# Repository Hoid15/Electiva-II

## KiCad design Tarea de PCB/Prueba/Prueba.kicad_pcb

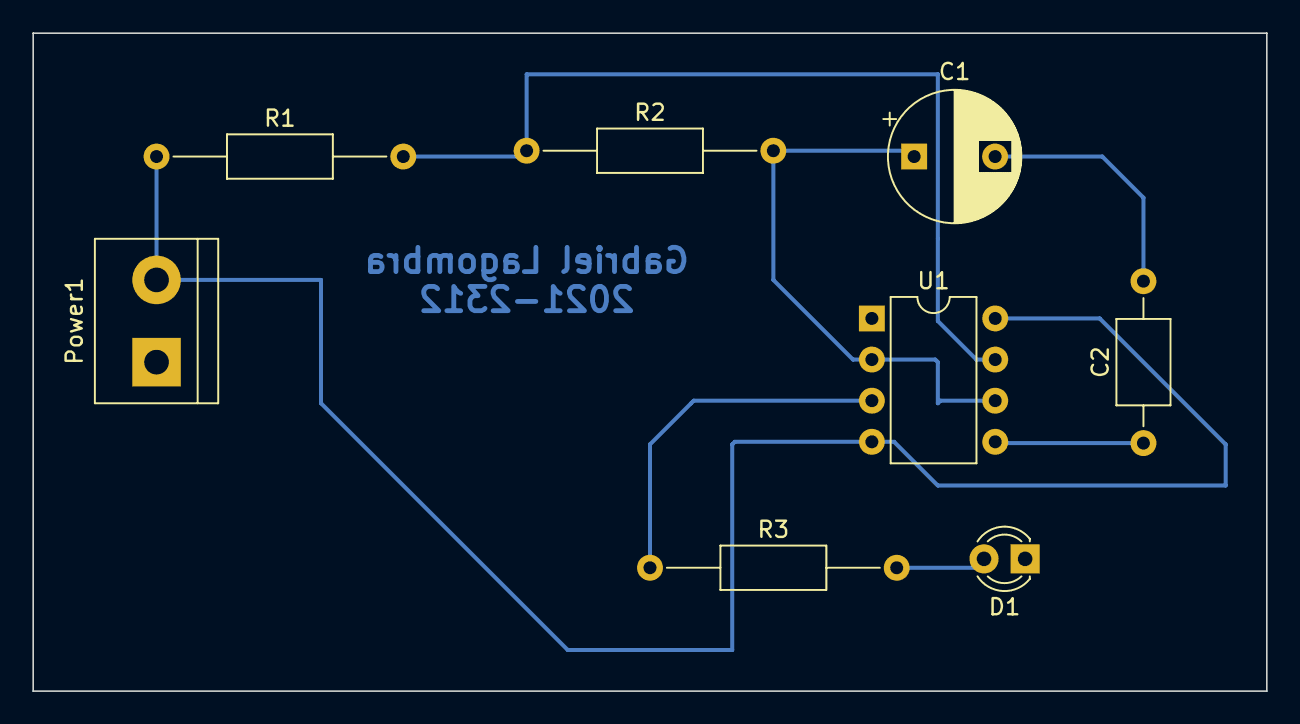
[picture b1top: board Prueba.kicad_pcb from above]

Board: 2 copper layers, 76.2 x 40.6 mm, 8 parts (0 on the bottom side), 7 nets.

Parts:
C1: 47uf; CP_Radial_D8.0mm_P5.00mm
C2: 100nf; C_Axial_L5.1mm_D3.1mm_P10.00mm_Horizontal
D1: LED; LED_D3.0mm
Power1: Screw_Terminal_01x02; TerminalBlock_bornier-2_P5.08mm
R1: 2.2K; R_Axial_DIN0207_L6.3mm_D2.5mm_P15.24mm_Horizontal
R2: 3.3K; R_Axial_DIN0207_L6.3mm_D2.5mm_P15.24mm_Horizontal
R3: 330; R_Axial_DIN0207_L6.3mm_D2.5mm_P15.24mm_Horizontal
U1: LM555xN; DIP-8_W7.62mm

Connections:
5+V: Power1.2, R1.1, U1.4 (R), U1.8 (VCC)
Led1: R3.1, U1.3 (Q)
unnamed: D1.2 (A), R3.2
unnamed: C2.1, U1.5 (CV)
SA2-6: C1.1, R2.2, U1.2 (TR), U1.6 (THR)
SA7: R1.2, R2.1, U1.7 (DIS)
gnd: C1.2, C2.2, D1.1 (K), Power1.1, U1.1 (GND)

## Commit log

2024-05-17 Add files via upload
    definición de complejidad, Tarea #1
2024-05-24 Add files via upload
    Tarea#2
2024-05-31 Tarea de PCB
    https://www.youtube.com/watch?v=vtUj1Ba_ELk&t=381s
    https://www.youtube.com/watch?v=7YaQ3QVPdN0&t=899s
2024-08-10 Asignaciones del grupo de manual y etiqueta
